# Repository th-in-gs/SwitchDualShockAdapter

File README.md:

# SwitchDualShockAdapter

A work-in-progress Dual Shock to Switch controller adapter using an ATMega8A and V-USB.

I'm documenting the project on my blog, https://www.blog.montgomerie.net/tags/switch-dual-shock-adapter-series/.

# Acknowledgements

This project is designed to be compiled by the PlatformIO system (https://platformio.org).

This project depends upon Objective Development's V-USB (https://www.obdev.at/vusb/) - see the `v-usb` directory.

This project depends upon the MiniCore implementation of the Arduino framework (https://github.com/MCUdude/MiniCore).

# Copyright

Copyright 2023 James Montgomerie.

This project is distributed under the terms of the GNU General Public License (see LICENSE.txt), in order to comply with the licensing conditions of its dependencies (see 'Acknowledgements').

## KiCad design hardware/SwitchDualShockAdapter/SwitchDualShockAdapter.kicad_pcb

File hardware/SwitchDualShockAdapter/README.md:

KiCad project, with schematic and PCB layout.
The PCB should be run through the "Round Tracks" plugin before production.
The components associated with the two LEDs are optional, as are one of either the USB header or USB-C port

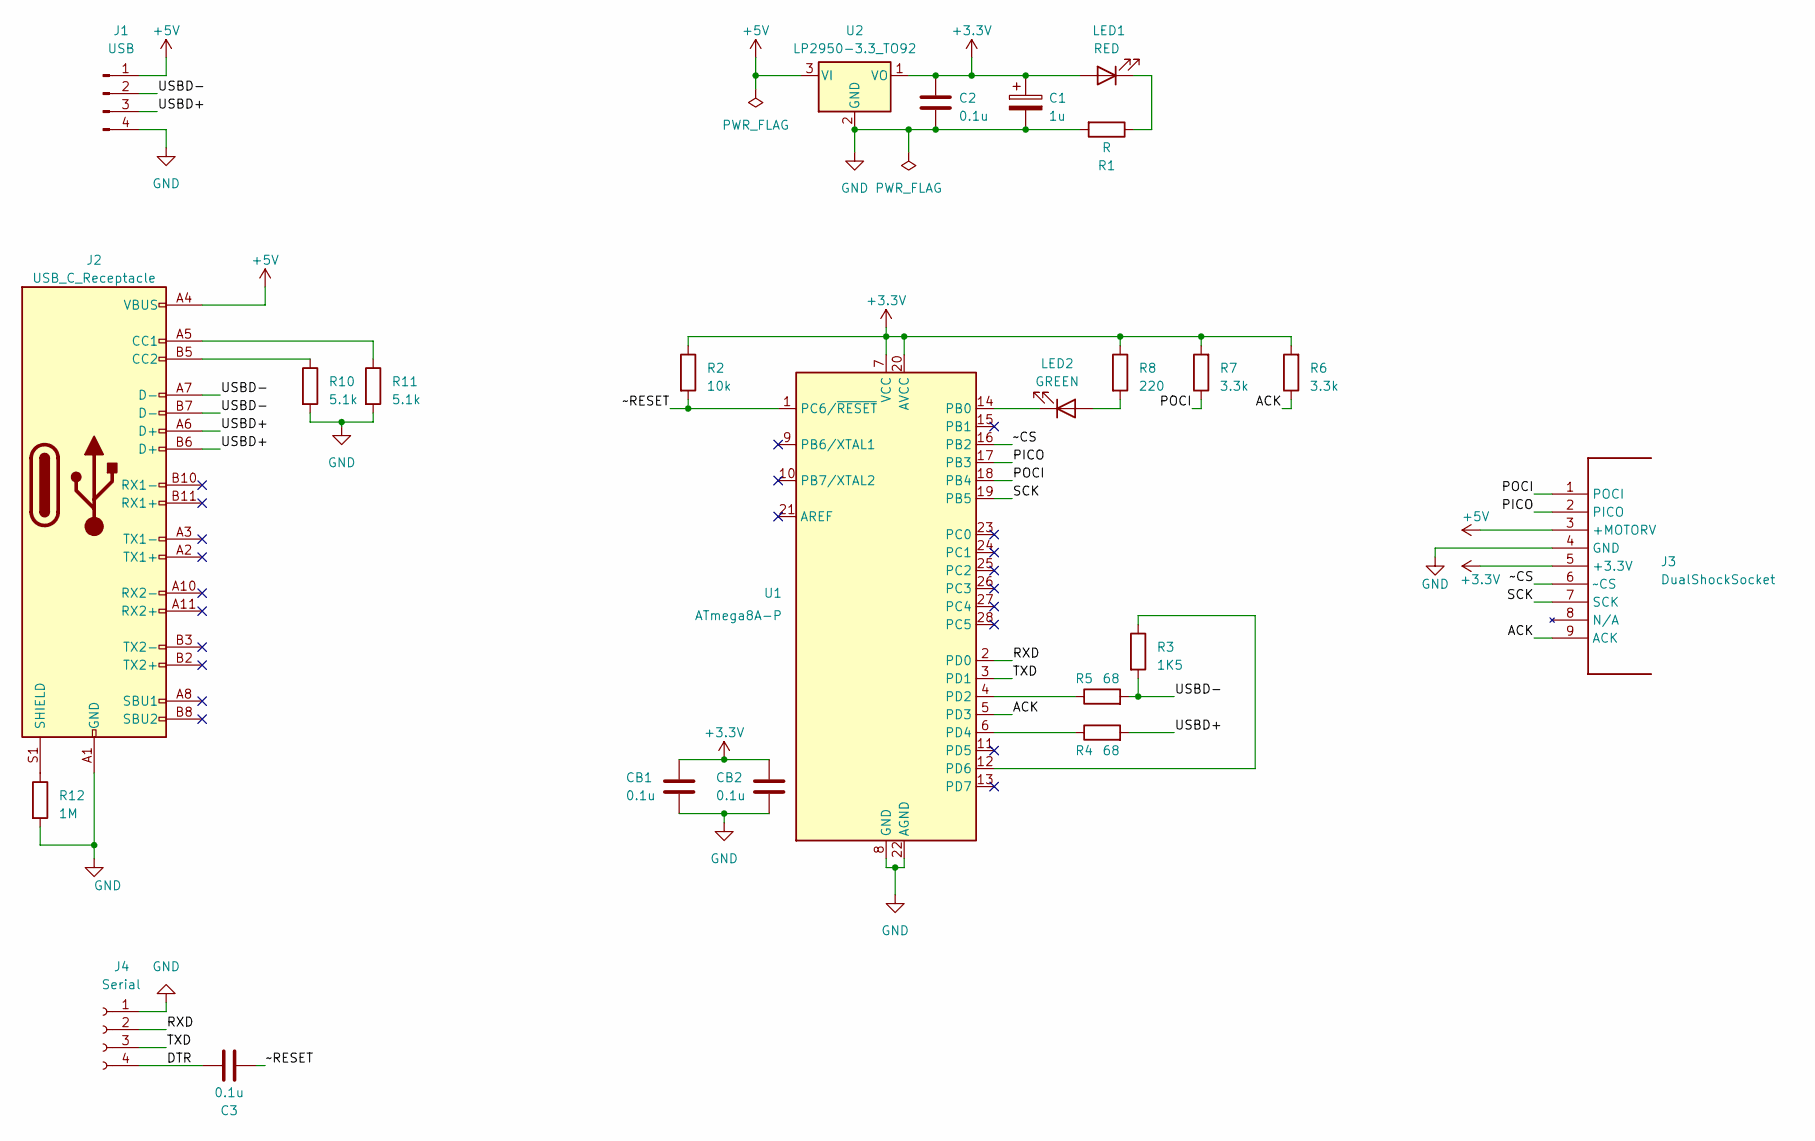
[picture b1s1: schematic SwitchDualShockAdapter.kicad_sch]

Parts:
C1: 1u; CP_Radial_D5.0mm_P2.00mm
C2, C3: 0.1u; C_Disc_D5.0mm_W2.5mm_P2.50mm
CB1, CB2: 0.1u; C_Disc_D5.0mm_W2.5mm_P2.50mm
J1: USB; PinHeader_1x04_P2.54mm_Vertical
J2: USB_C_Receptacle; TYPE-C-31-M-04
J3: DualShockSocket
J4: Serial; PinSocket_1x04_P2.54mm_Vertical
LED1: RED; LED_D5.0mm
LED2: GREEN; LED_D5.0mm
R1: R; R_Axial_DIN0207_L6.3mm_D2.5mm_P7.62mm_Horizontal
R2: 10k; R_Axial_DIN0207_L6.3mm_D2.5mm_P7.62mm_Horizontal
R3: 1K5; R_Axial_DIN0207_L6.3mm_D2.5mm_P7.62mm_Horizontal
R4, R5: 68; R_Axial_DIN0207_L6.3mm_D2.5mm_P7.62mm_Horizontal
R6, R7: 3.3k; R_Axial_DIN0207_L6.3mm_D2.5mm_P7.62mm_Horizontal
R8: 220; R_Axial_DIN0207_L6.3mm_D2.5mm_P7.62mm_Horizontal
R10, R11: 5.1k; R_Axial_DIN0207_L6.3mm_D2.5mm_P7.62mm_Horizontal
R12: 1M; R_Axial_DIN0207_L6.3mm_D2.5mm_P7.62mm_Horizontal
U1: ATmega8A-P; DIP-28_W7.62mm
U2: LP2950-3.3_TO92; TO-92_Inline

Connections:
+3.3V: C1.1, C2.1, CB1.1, CB2.1, J3.5 (+3.3V), LED1.2 (A), R2.1, R6.2, R7.2, R8.1, U1.7 (VCC), U1.20 (AVCC), U2.1 (VO)
+5V: J1.1, J2.A4 (VBUS), J2.A9 (VBUS), J2.B4 (VBUS), J2.B9 (VBUS), J3.3 (+MOTORV), U2.3 (VI)
/ACK: J3.9 (ACK), R6.1, U1.5 (PD3)
/DTR: C3.2, J4.4
/PICO: J3.2 (PICO), U1.17 (PB3)
/POCI: J3.1 (POCI), R7.1, U1.18 (PB4)
/RXD: J4.2, U1.2 (PD0)
/SCK: J3.7 (SCK), U1.19 (PB5)
/TXD: J4.3, U1.3 (PD1)
/USBD+: J1.3, J2.A6 (D+), J2.B6 (D+), R4.2
/USBD-: J1.2, J2.A7 (D-), J2.B7 (D-), R3.2, R5.2
/~CS: J3.6 (~CS), U1.16 (PB2)
/~RESET: C3.1, R2.2, U1.1 (PC6/~RESET)
GND: C1.2, C2.2, CB1.2, CB2.2, J1.4, J2.A1 (GND), J2.A12 (GND), J2.B1 (GND), J2.B12 (GND), J3.4 (GND), J4.1, R1.2, R10.2, R11.2, R12.2, U1.8 (GND), U1.22 (AGND), U2.2 (GND)
unnamed: J2.A5 (CC1), R11.1
unnamed: J2.B5 (CC2), R10.1
unnamed: J2.31, J2.32, J2.S1 (SHIELD), R12.1
unnamed: LED1.1 (K), R1.1
unnamed: LED2.2 (A), R8.2
unnamed: LED2.1 (K), U1.14 (PB0)
unnamed: R5.1, U1.4 (PD2)
unnamed: R4.1, U1.6 (PD4)
unnamed: R3.1, U1.12 (PD6)

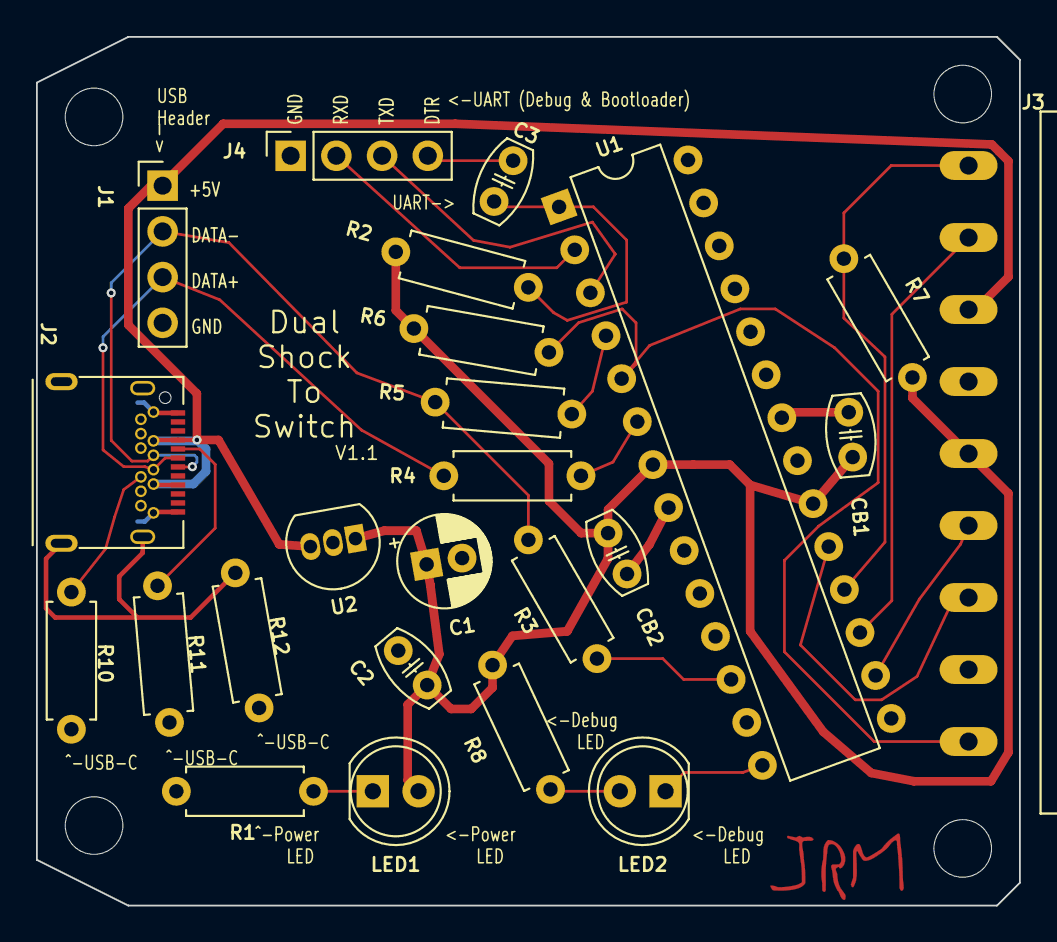
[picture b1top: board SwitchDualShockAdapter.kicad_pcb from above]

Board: 2 copper layers, 54.6 x 48.3 mm, 24 parts (0 on the bottom side), 23 nets.

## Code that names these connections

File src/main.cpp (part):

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    // Set port 2 outputs. Most of these pins are prescribed by the ATmega's
    // built in SPI communication hardware.
    DDRB |=
        1 << 5 | // SCK (PB5) - Serial data clock.
        1 << 3 | // PICO (PB3) - Serial data from ATmega to controller.
        1 << 2 | // Use PB2 for the controller's 'Chip Select' line
        1 << 0   // PB0 for our blinking debug LED.
    ;

    // Set up the SPI Control Register. Form right to left:
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    while(true);
}

// The Dual Shock's ACK line is connected to pin 5, INT1.
static volatile bool sDualShockAcknowledgeReceived = false;
ISR(INT1_vect, ISR_NOBLOCK)
{
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    sReportPending = true;
}

static void prepareUartReplyReport_F(uint8_t ack, uint8_t subCommand, const uint8_t *reportIn, uint8_t reportInLen,  void *(*copyFunction)(void *, const void *, size_t))
{
    // '_F' - means pass in function to use for memcpying.

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    sReportPending = true;
}

static void prepareUartReplyReport_P(uint8_t ack, uint8_t subCommand, const uint8_t *reportIn, uint8_t reportInLen)
{
    return prepareUartReplyReport_F(ack, subCommand, reportIn, reportInLen, memcpy_P);
}

static void prepareUartReplyReport(uint8_t ack, uint8_t subCommand, const uint8_t *reportIn, uint8_t reportInLen)
{
    return prepareUartReplyReport_F(ack, subCommand, reportIn, reportInLen, memcpy);
}
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
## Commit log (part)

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2008-04-17 - used wrong name in copy -- fixed this
2008-04-18 - documented changes and release
2008-04-18 - updated version number
2008-04-30 - some code size optimizations
2008-05-03 - added new config option for long transfers
2008-05-03 - introduced usbTxStatus structure and used it for interrupt-in endpoints
2008-05-03 - documented changes
2008-05-03 - documentation update
2008-05-13 - added 20 MHz module
2008-05-13 - documented 20 MHz module
2008-05-13 - enabled keyword expansion on *.inc files - updated version constant in header
2008-06-17 - removed iarcompat.h in favor of usbportability.h which is intended to take care of ports to other compilers such as CodeVision as well.
2008-06-18 - extended concept of usbportability header: moved all portability stuff there
2008-07-14 - use control transfers to USB_RECIP_DEVICE instead of USB_RECIP_INTERFACE so that we need not claim the interface.
2008-10-08 - improved wording of license text
2008-10-13 - improved docs for descriptor property flags
2008-10-13 - new transmitter routine is much shorter - endm statement must be prefixed with spaces for IAR
2008-10-13 - endm statement must be prefixed with spaces for IAR
2008-10-17 - added 12.8 MHz PLL module
2008-10-18 - updated general comments
2008-10-18 - Added documentation for 12.8 MHz module
2008-10-18 - fixed jump target for SE0 computation in bitIsSet branch
2008-10-20 - optimization: 3 x nop2 = 2 x lpm
2008-10-20 - use timeout in waitForJ
2008-10-20 - more precise comment
2008-10-20 - optimized 4 more bytes
2008-10-20 - improved waitForJ loop by 1 instruction
2008-10-20 - Added reference to Henrik Haftmann for oscillator sync
2008-10-22 - replaced a nop nop with nop2
2008-10-22 - USB_CFG_HAVE_INTRIN_ENDPOINT3 defaults to 0
2008-11-03 - no offset of 0x20 needed if symbol is a memory address.
2008-11-07 - allow distribution under GPLv3 as well
2009-03-16 - debug print CRC as well, not just message.
2009-03-23 - documentation updates
2009-04-13 - great renaming: project is now renamed from AVR-USB to V-USB
2009-04-15 - entered release date
2009-08-03 - added comment how USB port pins must be initialized
2009-08-03 - formating...
2009-08-06 - minor code optimization
2009-08-09 - fixed duration of unstuffing routine for bit 6 (was one cycle too long)
2009-08-22 - fixed bmAttributes in configuration descriptor
2009-08-22 - documentation updates for clay logic and USB-IDs
2009-08-22 - changed release date
2010-01-15 - fixed define for interrupt vector (default vector used)
2010-01-15 - removed file: We only have infos now, no license
2010-01-25 - no more default for USB_CFG_CLOCK_KHZ
2010-01-25 - removed comment about default fro USB_CFG_CLOCK_KHZ
2010-05-30 - introduced USB_CFG_DRIVER_FLASH_PAGE config option
2010-07-15 - take endpoint 3 number from USB_CFG_EP3_NUMBER for config descriptor
2010-07-15 - fixed release date
2010-12-22 - fixed hex translation of some USB IDs, there was a typo
2012-01-08 - Added rules for standard mice, keyboards etc.
2012-01-09 Improved change description in Changelog.txt
2012-01-09 RELEASE: Added release date to Changelog.txt
2012-07-09 Changed Clay Logic to flirc.tv, Inc.
    Jason Kotzin is now working as flirc.tv and we have updated our documentation.
2012-12-05 usbMsgPtr now has a separate type so that it can be defined to an 8 bit type for tiny memory model
2012-12-05 Removed unnecessary include of usbportability.h.
    This include caused a header dependency problem. usbconfig.h must be included before usbportability.h because the PROGMEM macros must know the size of the memory model. usbdrv.h includes the headers 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
2012-12-05 Removed all references to the SVN expansion keyword $Id$.
2012-12-05 Documented changes in Changelog.
2013-11-12 Made usbSetInterrupt() tolerant to zero sized blocks.
2013-11-12 Added #ifdef and extern "C" so that usbdrv.h / usbdrv.c can be included from C++ module.
2013-11-28 For compatibility reasons define usbMsgPtr_t to char * by default.
    Using unsigned short would generate smaller code, but causes warnings with existing projects.
2013-11-28 Added long-pending 18 MHz module without CRC.
    This module was contributed by Lukas Schrittwieser as a complement to the 18 MHz module including a CRC check.
    It is useful for boot loaders on boards which run on 18 MHz because they use the CRC module in the main code.
2015-09-04 For bus-powered devices add the "Remote Wake" attribute to the configuration descriptor.
2017-01-24 `USB_CFG_DESCR_PROPS_UNKNOWN` now honors the `USB_PROP_IS_RAM` flag.
2018-05-22 Added more free USB-IDs
2020-10-21 Fixed comments indicating CPU cycles taken.
    ST instruction uses two cycles while LDI takes one.
2022-11-29 Initial empty commit
2022-12-03 Set up PlatformIO for ATMega8A project.
2022-12-03 Configuration and a blinking LED!
2022-12-04 It compiles with V-USB!
2022-12-04 Squashed 'v-usb/' content from commit 7a28fdc
    git-subtree-dir: v-usb
    git-subtree-split: 7a28fdc685952412dad2b8842429127bc1cf9fa7
2022-12-04 Squashed 'v-usb/' content from commit 02a5d29
    git-subtree-dir: v-usb
    git-subtree-split: 02a5d29642149a4159da735285b952c4d0367c9b
2022-12-05 V-USB configuration. 'Do-Nothing' use of V-USB.
2022-12-05 Make the heartbeat function static.
2022-12-07 Add '-e' flag to upload flags.
    From the avrdude docs: "Causes a chip erase to be executed. This will reset the contents of the flash ROM and EEPROM to the value `0xff', and clear all lock bits. Except for ATxmega devices which can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
    prerequisite command before the flash ROM can be reprogrammed again. The only exception would be if the new contents would exclusively cause bits to be programmed from the value `1' to `0'."
2022-12-11 Abortive attempts at Pro Controller communication
2022-12-11 Fake HID controller working.
2022-12-15 Save a few bytes.
2022-12-15 A little cleanup. Print update radar on LCD.
2022-12-15 A little cleanup.
2022-12-16 Trying to make communication more reliable.
2022-12-17 A little bit more clearnup and commentary. Handle 0x21 explicitly (but just return success!) - the Switch seemed to be sending these a lot and this quietens it down...
2022-12-21 Documentation updates.
2022-12-21 Updates to platformio.ini after more testing.
2022-12-21 Add a README.md file. More blog writing.
2022-12-22 Update Log 1 with edits form blog repo.
2022-12-25 Updates to first blog post.
2022-12-25 Add symlinks in `lib` folder to appropriate V-USB locations.
2022-12-25 V-USB working with 12.8MHz calibration. Data pin connections changed in V-USB configuration, and calibration routines included. main.cpp updated.
2022-12-28 Working Dual Shock to Switch conversion! Needs cleaning up and making more friendly (e.g. make analog mode be entered automatically).
2022-12-29 A little cleanup. Switch off USB_CFG_HAVE_FLOWCONTROL.
2022-12-31 Revert "Work on hang error. Turns out it might all just be because of the timing being off because of the serial output!?"
    This reverts commit e4f6621e0c4e36e6312164fe7e86283fce740181.
2022-12-31 Revert "Work on hang error. Turns out it might all just be because of the timing being off because of the serial output!?"
    This reverts commit 27234985bf56b74c785cba3739192ec6eb484ec1.
2022-12-31 May as well use the fast CRC routines.
2022-12-31 Zero out analog sticks if the Dual Shock is not reporting them.
2023-01-02 A lot of changes. All sending now in one loop. Prints the elapsed SOF count for each loop, and it's really strance! On the internal connector, there are very often 1, and sometimes up to 3 sofs betwe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
2023-01-09 Switch to using 16MHz crystal. Extra SOFs (i.e. at more than a 1MHz rate) seem to be making the self-calibration unstable enough to affect USB communication.
2023-01-09 Correct BOD and BODLEVEL definitions.
2023-01-09 Fix some UART responses, notably 0x21 "Set NFC/IR MCU config". Cleanup (boolean -> bool) and some performance improvements. Add some debug logs.
2023-01-09 Rename Log 3 to Log 4 - making room for an intermediate post.
2023-01-11 Part 3 blog post. A little modificaiton to the video in the part 2 post.
2023-04-08 Controlling a Nintendo Switch. For now, just alternately presses left and right on the dpad as a proof of concept.
2023-04-24 Add debug outputs.
2023-04-25 Add serial debugging output, and clean up some misunderstandings about the Pro Controller communication protocol found while using it.
2023-04-26 Implement resetting of reception on endpoint 1 on HALT state.
2023-04-26 Instrument interrupt routines to output more debug information on PORTC. - Bit 0 is toggled when V-USB detects a SOF keep-alive pulse. - Bit 1 is set while V-USB is in its interrupt routine (i.e. pro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
2023-04-27 Switch off interrupts during MiniCore's (The Arduino framework) Timer0 intrerrupt routine, and switch back to using the inernal oscilator.
2023-04-27 Clean up USB_SOF_HOOK handling, leaving debut output in place.
2023-05-03 Only send the part of the report that actually contains useful information. Allow us to reach over 120 updates per second!
2023-05-05 Switch to using a serial bootloader.
    The new 'ATmega8Bootloader' environment contains the correct settings for setting up the bootloader. Put an ATMega8A in an ISP programmer then:
    > pio run -e ATmega8Bootloader -t bootloader
    Then connect a USB serial convertor to it, with a 0.1uf cap between DTR and the (pulled-up) ground connection, and the usual upload command will upload to it:
    > pio run -t upload
2023-05-06 Talk with a Dual Shock, and correctly translate to Switch reports.
2023-05-07 Small bits of cleanup.
2023-05-07 More verbose readme.
2023-05-07 Dead zone was far too small. Forgot to square the radius when implementing the circular dead zone!
2023-05-08 Don't poll the Dual Shock until _just_ before we're about to send the report.
2023-05-09 Move all USB handling into one main loop, in perparation for handling USB suspension.
2023-05-09 Small comment changes.
2023-05-15 Remove unused (and wrong!) debug macro.
2023-05-16 Change fuse settings for a 512 byte (256 word) bootloader, instead of a 512 word one.
2023-05-16 Working over USB suspend. Of note:
    - New basic serial output routines to use instead of the Arduino ones. They are interrupt-free. I was finding that USB communication was
    becoming unreliable with serial debugging on. I believe the cause was MiniCore's use of the USB transmission interrupt.
    - Turns out the reportreception routine can use teh usual USB mechanism to know when reports are done (short packet or full length received), but I needed to increase the interrupt frequency for the 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
    /Stalls.
    - A few other reliability changes in usbFunctionWriteOutOrAbandon that were necessary for the controller to work after wake.
2023-05-17 USB resume doesn't seem to work on Switch :-(
2023-05-17 Power save mode on USB suspend.
2023-05-17 Move timer routined to their own file.
2023-05-18 Comment corrections and some code reordering for clarity.
2023-05-20 First dumb attempt at rumble decoding...
2023-05-23 Rumble fully decoded. Switched to a new packed strings format for debug strings to save program space.
2023-06-01 Better Dual Shock error handling.
2023-06-02 Improved error checking added recently broke the ANALOG -> Home Button mapping.
2023-06-02 Add KiCad project - schematic and PCB.
2023-06-13 Use both motors for all rumble if possible. Add a default OSCCAL for ATmega88.
2023-06-13 Switch the debug LED on immediately when a USB connection is detected.
2024-11-20 Better 8 to 12 bit conversion. Change some other things to save some flash space to give room.
2024-11-20 Split SPI memory into seperate file.
2024-11-22 Allow the Switch to write calibration data to the ATMega's EEPROM. Comment some of the SPI data.
2024-11-26 Mark some variables as const.
2024-11-26 Save two bytes in the compiled binary :-)
2025-11-26 Generate MAC at compile time.
